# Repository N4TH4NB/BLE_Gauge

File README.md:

## Bluetooth Gauge

*Texto q vou adicionar dps*

This project was initially based on the American Embedded KiCad Template,
available at:
https://github.com/i2cjak/American_Embedded_KiCad_Template

The original project is licensed under CERN-OHL-P-2.0.

This project has been modified and adapted for its specific purpose.

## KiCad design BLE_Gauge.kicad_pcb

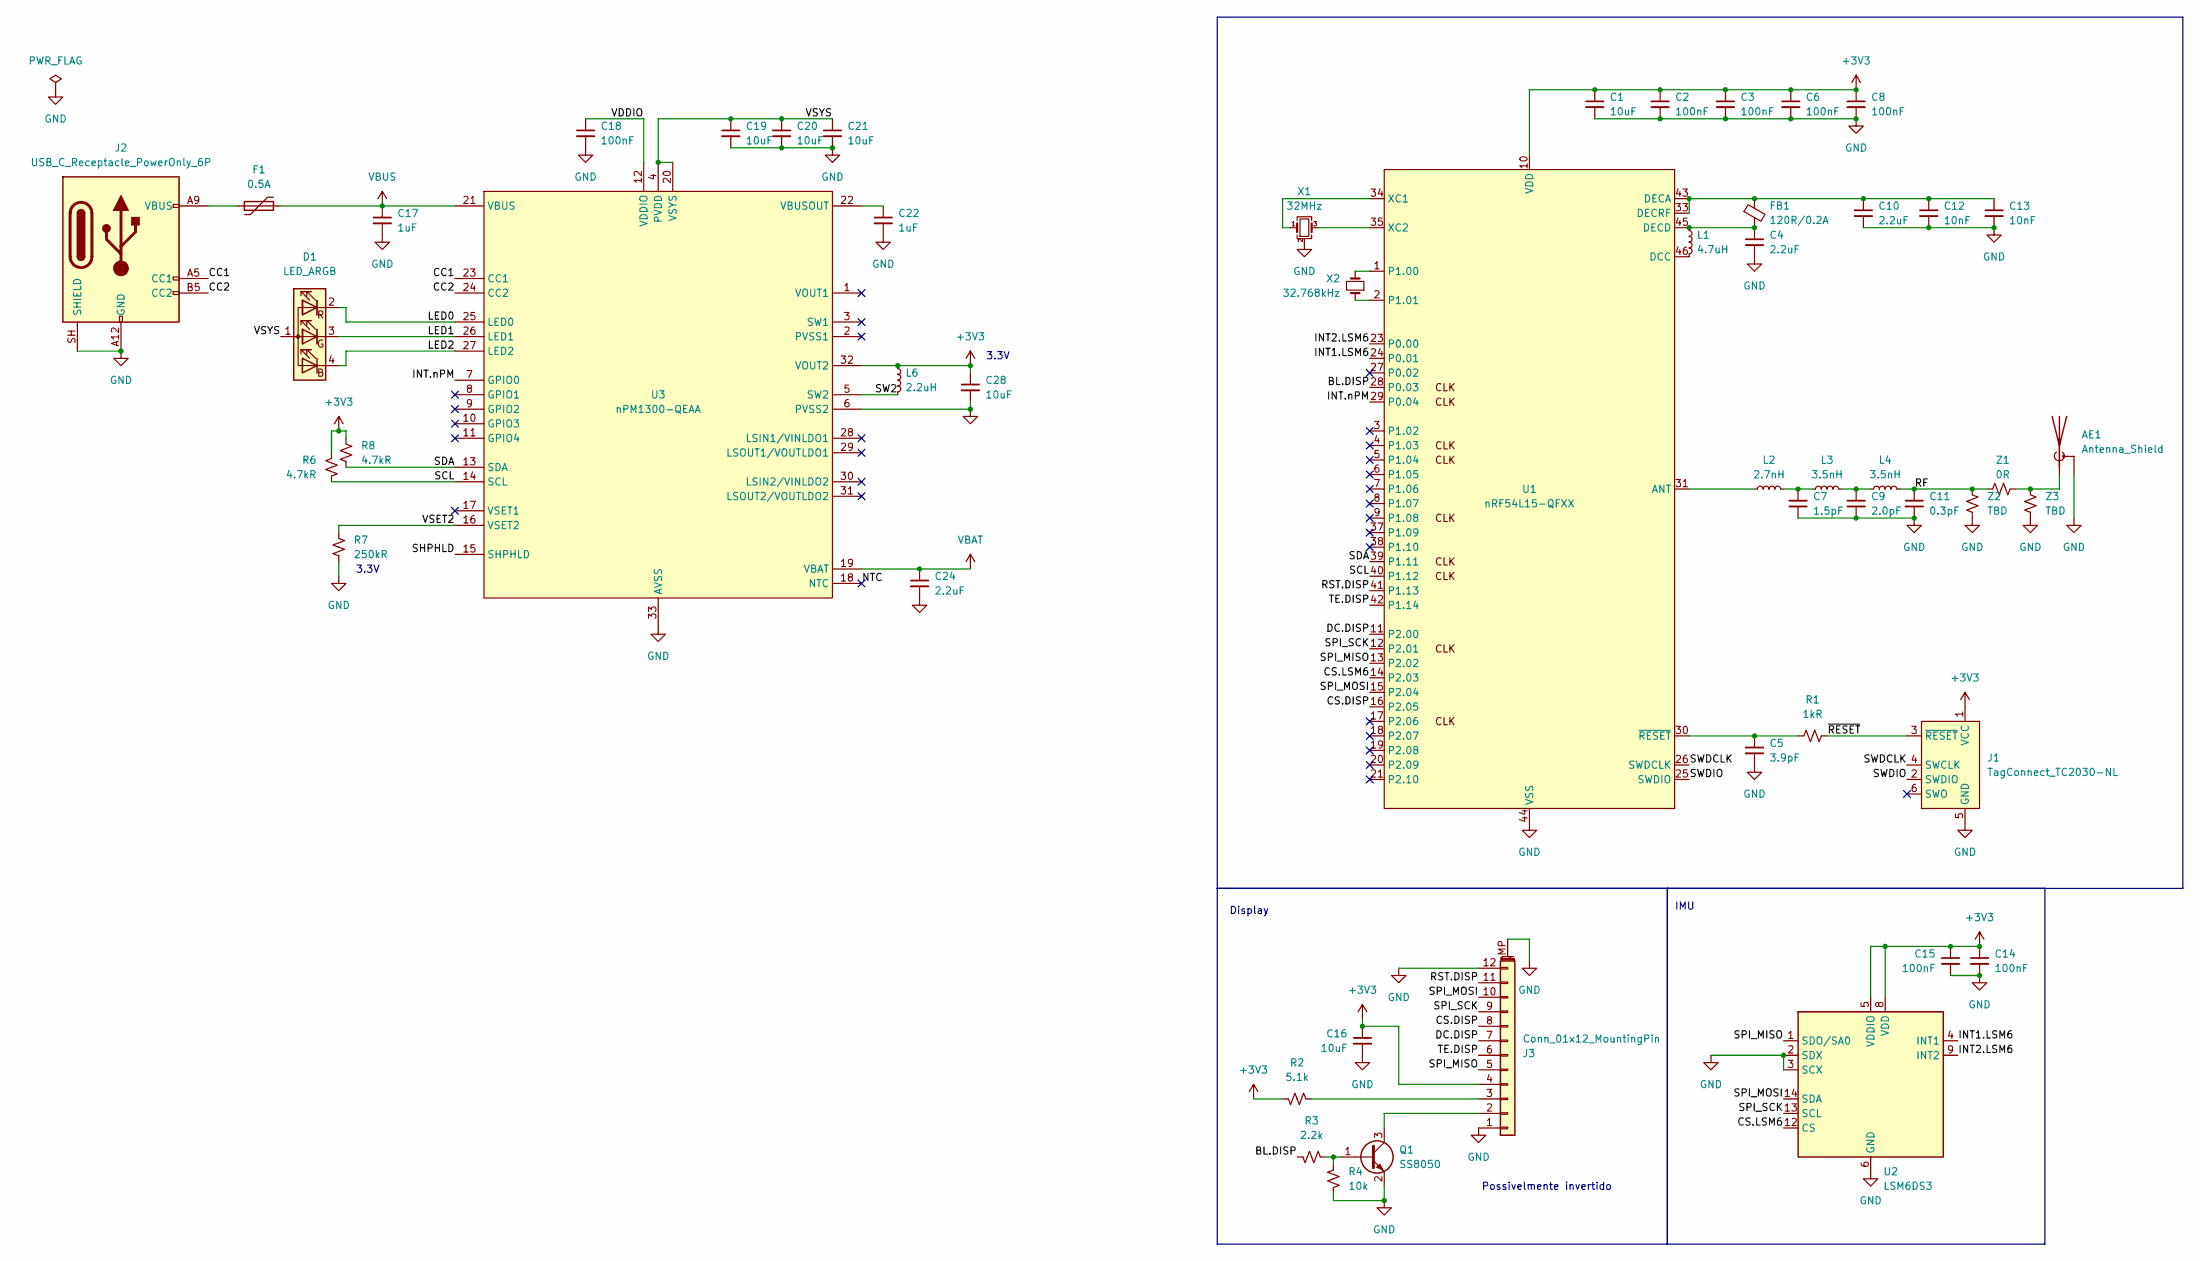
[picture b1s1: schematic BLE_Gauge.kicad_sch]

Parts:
AE1: Antenna_Shield; Texas_SWRA117D_2.4GHz_Right
C1: 10uF; C_0402_1005Metric_Nordic
C2, C3, C6, C8, C18: 100nF; C_0201_0603Metric_Nordic
C4, C10: 2.2uF; C_0201_0603Metric_Nordic
C5: 3.9pF; C_0201_0603Metric_Nordic
C7: 1.5pF; C_0201_0603Metric_Nordic
C9: 2.0pF; C_0201_0603Metric_Nordic
C11: 0.3pF; C_0201_0603Metric_Nordic
C12, C13: 10nF; C_0201_0603Metric_Nordic
C14, C15: 100nF; C_0201_0603Metric
C16: 10uF; C_0402_1005Metric
C17, C22: 1uF; C_0603_1608Metric_Nordic
C19, C20, C21, C28: 10uF; C_0603_1608Metric_Nordic
C24: 2.2uF; C_0603_1608Metric_Nordic
D1: LED_ARGB
F1: 0.5A; Fuse_0603_1608Metric
FB1: 120R/0.2A; L_0201_0603Metric_Nordic
J1: TagConnect_TC2030-NL; Tag-Connect_TC2030-IDC-NL_2x03_P1.27mm_Vertical
J2: USB_C_Receptacle_PowerOnly_6P; USB_C_Receptacle_GCT_USB4125-xx-x-0190_6P_TopMnt_Horizontal
J3: Conn_01x12_MountingPin; Hirose_FH12-12S-0.5SH_1x12-1MP_P0.50mm_Horizontal
L1: 4.7uH; L_0603_1608Metric_Nordic
L2: 2.7nH; L_0201_0603Metric_Nordic
L3, L4: 3.5nH; L_0201_0603Metric_Nordic
L6: 2.2uH; L_0806_2016Metric_Nordic
Q1: SS8050; SOT-23
R1: 1kR; R_0201_0603Metric_Nordic
R2: 5.1k; R_0201_0603Metric
R3: 2.2k; R_0201_0603Metric
R4: 10k; R_0201_0603Metric
R6, R8: 4.7kR; R_0201_0603Metric_Nordic
R7: 250kR; R_0201_0603Metric_Nordic
U1: nRF54L15-QFXX; QFN-48-1EP_6x6mm_P0.4mm_EP4.6x4.6mm_ThermalVias
U2: LSM6DS3; LGA-14_3x2.5mm_P0.5mm_LayoutBorder3x4y
U3: nPM1300-QEAA; QFN-32-1EP_5x5mm_P0.5mm_EP3.6x3.6mm_ThermalVias
X1: 32MHz; Crystal_SMD_2016-4Pin_2.0x1.6mm
X2: 32.768kHz; Crystal_SMD_2012-2Pin_2.0x1.2mm
Z1: 0R; C_0201_0603Metric
Z2, Z3: TBD; C_0201_0603Metric

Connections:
+3V3: C1.1, C2.1, C3.1, C6.1, C8.1, C14.1, C15.1, C16.1, C28.1, J1.1 (VCC), J3.4, L6.1, R2.2, R6.1, R8.1, U1.10 (VDD), U1.22 (VDD), U1.36 (VDD), U1.47 (VDD), U1.48 (VDD), U2.5 (VDDIO), U2.8 (VDD), U3.32 (VOUT2)
/BL.DISP: R3.2, U1.28 (P0.03)
/CC1: J2.A5 (CC1), U3.23 (CC1)
/CC2: J2.B5 (CC2), U3.24 (CC2)
/CS.DISP: J3.8, U1.16 (P2.05)
/CS.LSM6: U1.14 (P2.03), U2.12 (CS)
/DC.DISP: J3.7, U1.11 (P2.00)
/INT1.LSM6: U1.24 (P0.01), U2.4 (INT1)
/INT2.LSM6: U1.23 (P0.00), U2.9 (INT2)
/INT.nPM: U1.29 (P0.04), U3.7 (GPIO0)
/LED0: D1.2 (RK), U3.25 (LED0)
/LED1: D1.3 (GK), U3.26 (LED1)
/LED2: D1.4 (BK), U3.27 (LED2)
/NTC: U3.18 (NTC)
/RF: C11.1, L4.2, Z1.2, Z2.2
/RST.DISP: J3.11, U1.41 (P1.13)
/SCL: R6.2, U1.40 (P1.12), U3.14 (SCL)
/SDA: R8.2, U1.39 (P1.11), U3.13 (SDA)
/SHPHLD: U3.15 (SHPHLD)
/SPI_MISO: J3.5, U1.13 (P2.02), U2.1 (SDO/SA0)
/SPI_MOSI: J3.10, U1.15 (P2.04), U2.14 (SDA)
/SPI_SCK: J3.9, U1.12 (P2.01), U2.13 (SCL)
/SW2: L6.2, U3.5 (SW2)
/SWDCLK: J1.4 (SWCLK), U1.26 (SWDCLK)
/SWDIO: J1.2 (SWDIO), U1.25 (SWDIO)
/TE.DISP: J3.6, U1.42 (P1.14)
/VDDIO: C18.1, U3.12 (VDDIO)
/VSET2: R7.1, U3.16 (VSET2)
/VSYS: C19.1, C20.1, C21.1, D1.1 (A), U3.4 (PVDD), U3.20 (VSYS)
/~RESET: J1.3 (~RESET), R1.2
GND: AE1.2 (Shield), C1.2, C2.2, C3.2, C4.2, C5.2, C6.2, C7.2, C8.2, C9.2, C10.2, C11.2, C12.2, C13.2, C14.2, C15.2, C16.2, C17.2, C18.2, C19.2, C20.2, C21.2, C22.2, C24.2, C28.2, J1.5 (GND), J2.A12 (GND), J2.B12 (GND), J2.SH (SHIELD), J3.1, J3.12, J3.MP (MountPin), Q1.2 (E), R4.2, R7.2, U1.32 (VSS_PA), U1.44 (VSS), U1.49 (VSS), U2.2 (SDX), U2.3 (SCX), U2.6 (GND), U2.7 (GND), U3.6 (PVSS2), U3.33 (AVSS), X1.2 (G), X1.4 (G), Z2.1, Z3.1
unnamed: AE1.1 (A), Z1.1, Z3.2
unnamed: C7.1, L2.2, L3.1
unnamed: C9.1, L3.2, L4.1
unnamed: F1.1, J2.A9 (VBUS), J2.B9 (VBUS)
unnamed: J3.2, Q1.3 (C)
unnamed: J3.3, R2.1
unnamed: Q1.1 (B), R3.1, R4.1
unnamed: L2.1, U1.31 (ANT)
unnamed: L1.2, U1.46 (DCC)
unnamed: C10.1, C12.1, C13.1, FB1.1, U1.33 (DECRF), U1.43 (DECA)
unnamed: C4.1, FB1.2, L1.1, U1.45 (DECD)
unnamed: U1.1 (P1.00), X2.2
unnamed: U1.2 (P1.01), X2.1
unnamed: U1.34 (XC1), X1.1
unnamed: U1.35 (XC2), X1.3
unnamed: C5.1, R1.1, U1.30 (~RESET)
unnamed: C22.1, U3.22 (VBUSOUT)
VBAT: C24.1, U3.19 (VBAT)
VBUS: C17.1, F1.2, U3.21 (VBUS)

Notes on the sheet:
Display
3.3V
IMU
Possivelmente invertido

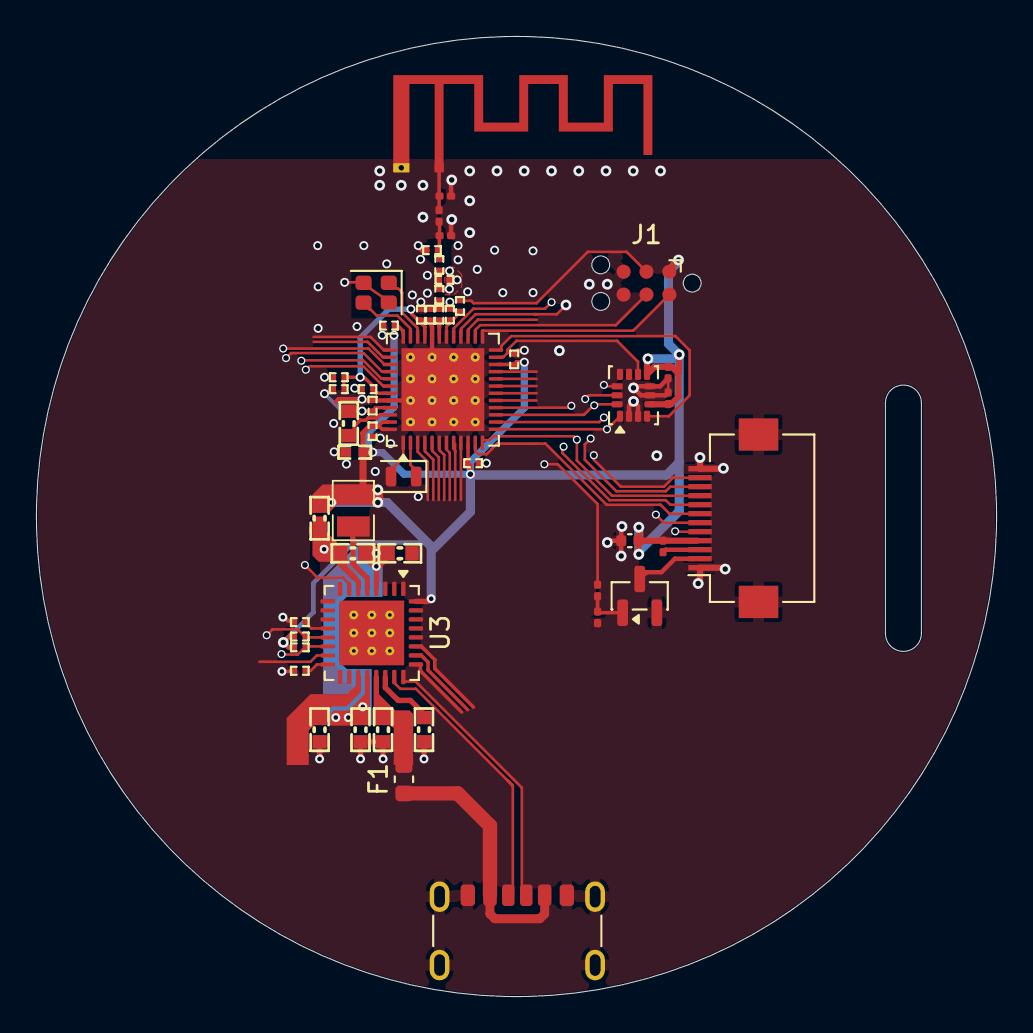
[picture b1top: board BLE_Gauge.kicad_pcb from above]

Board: 4 copper layers, 53.3 x 53.3 mm, 51 parts (0 on the bottom side), 45 nets.
